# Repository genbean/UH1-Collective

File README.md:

# Heli Collective

A 3D-printed, desk-mounted collective for helicopter flight simulators, modelled on the UH-1 "Huey". It plugs into a PC by USB and shows up as an ordinary game controller, so any sim can use it.

- **The lever** is a 25 mm carbon-fibre tube in a printed base that screws to the desk. It pivots on two ball bearings, a gas strut balances the head's weight, and a knob sets the friction. It travels 32° to a fixed stop. The lever is two-thirds as long as the real one and starts level, so your hand rises about as far as on a real Huey (9.4 in against 9.25 in).
- **The head** is the Huey's collective switch box: GOV RPM, landing light and search light toggles, the SEARCH CONT hat (an 8-way stick), the STOP REL button and the starter trigger. Under it, the twist-grip throttle turns 181° between two hard stops, idle and full open, and stays where you leave it.
- **Sensors:** two AS5600 magnetic angle sensors, one for the lever in the base and one for the throttle in the head. There are no potentiometers to wear out.
- **Electronics:** the HeliSR board, a small PCB that carries a Pro Micro, sits in the head. It reads 16 switch inputs, and the AS5600s over I²C on four sensor ports. Only the USB cable comes out of the base.
- **Software:** the HeliSR firmware and a Windows app, HeliSR Configurator. The app flashes the board, assigns each switch position to a game button and calibrates the axes. Both are based on FreeJoy.

**Interactive exploded views** (point at any part to see what it is): [the base](https://htmlpreview.github.io/?https://github.com/genbean/UH1-Collective/blob/main/Base/renders/rev4_exploded.html), [the base's lever](https://htmlpreview.github.io/?https://github.com/genbean/UH1-Collective/blob/main/Base/renders/rev4_lever_exploded.html), [the head](https://htmlpreview.github.io/?https://github.com/genbean/UH1-Collective/blob/main/Head/renders/HueyHeadR5_Exploded.html), [the head from behind](https://htmlpreview.github.io/?https://github.com/genbean/UH1-Collective/blob/main/Head/renders/HueyHeadR5_Exploded_Rear.html).

More pictures: [from the side](renders/HeliCollective_side.png) and [at the 32° stop](renders/HeliCollective_32deg.png). [`renders/HeliCollective_Assembly.glb`](renders/HeliCollective_Assembly.glb) is the whole collective in 3D; it opens in Windows 3D Viewer or any glTF viewer.

## The parts

Each folder has its own README with the details: how it works, printing, the parts it needs, assembly, and how to rebuild the files.

| Folder | What's in it |
|---|---|
| [`Base/`](Base/README.md) | **MkIII base, Rev 4.** 73 mm (2.87 in) wide, the lever centred on the tube: the pivot on thin-section bearings, the split lever, a shell that encloses it, the gas strut, the brake behind the hub, the stops and the collective's AS5600. Ready-to-print STLs, fit-test coupons, a STEP assembly, renders with every screw labelled, and the scripts that make them. |
| [`Head/`](Head/README.md) | **Huey head, Rev 5.** The switch box in one print, cut to the real UH-1 panels' dimensions, with the throttle grip and its gears, the throttle's AS5600, the starter trigger and the search light hat, and a collision check (`check_r5.py`). STLs and scripts. The BOM lists it. |
| [`PCB/HeliSR/`](PCB/HeliSR/README.md) | **HeliSR Rev 4.0 board.** Sixteen switch inputs, and four I²C ports for the AS5600s, through a PCA9546A switch, in place of the analog inputs. KiCad files, Gerbers, connector pinouts and the assembly order. |
| [`PCB/AS5600/`](PCB/AS5600/README.md) | **AS5600 sensor board Rev 1.0.** The AS5600 on a 23.24 mm square board that fits the base and head, read through a 6 × 2.5 mm diametric magnet, with a JST SH socket on the back that takes a 1:N jumper straight from a HeliSR AX port. Nothing to modify. KiCad files, Gerbers and how to build it. |
| [`PCB/SearchHat/`](PCB/SearchHat/README.md) | **SearchHat Rev 1.0: the SEARCH CONT hat's breakout board.** An ALPS RKJXM1015004 8-direction stick switch on a 22 × 29 mm board that screws to the lower panel's back, with a JST SH socket or wire pads. KiCad files, Gerbers, the pinout and how to build it. |
| [`BOM/`](BOM) | **The bill of materials for the whole collective:** [`Heli_Collective_BOM.xlsx`](BOM/Heli_Collective_BOM.xlsx): every part to buy, with part numbers, where it goes, where to buy it, how many and the price, and a sheet of the printed parts. [`tools/make_bom.py`](tools/make_bom.py) rewrites it (and checks the board's parts against the board file). |
| [`Software/`](Software/README.md) | **HeliSR firmware and HeliSR Configurator**, with their documentation in [`Software/docs/`](Software/docs) and example profiles, including one for this collective. |
| [`renders/`](renders) | Pictures and a 3D model of the complete collective: head Rev 5 on base Rev 4. [`Base/make_renders_r4.py`](Base/make_renders_r4.py) builds them, and base Rev 4's renders, exploded view and screw chart. [`make_diagrams.py`](renders/make_diagrams.py) draws the head's exploded views, screw maps and screw chart from that model. |

## What you need

The full list, with quantities, part numbers, links and prices, is the [BOM spreadsheet](BOM/Heli_Collective_BOM.xlsx). In outline:

**Electronics**
- The HeliSR Rev 4.0 PCB: send [`HeliSR_Rev4.0_Gerbers.zip`](PCB/HeliSR/HeliSR_Rev4.0_Gerbers.zip) to any PCB maker (2 layers, 39.3 × 33.6 mm).
- The SearchHat Rev 1.0 PCB, for the SEARCH CONT hat: send [`SearchHat_Rev1.0_Gerbers.zip`](PCB/SearchHat/SearchHat_Rev1.0_Gerbers.zip) the same way (2 layers, 22 × 29 mm). Its ALPS switch and JST socket are in the BOM.
- The parts that solder onto the HeliSR board, all from Mouser: the BOM lists them with their board positions.
- A **5 V / 16 MHz Pro Micro** (ATmega32U4). This build uses a USB-C clone; the 3.3 V / 8 MHz version isn't supported.
- Two AS5600 sensor boards: send [`AS5600_Rev1.0_Gerbers.zip`](PCB/AS5600/AS5600_Rev1.0_Gerbers.zip) the same way (2 layers, 23.24 mm square). Each takes an AS5600 chip, two 1206 capacitors and a JST SH socket, and goes with a 6 × 2.5 mm diametric magnet; all from Digi-Key.
- JST SR 1.0 mm cables for the board (the sensors' are **1:N** 4-pin jumpers), a 4-core ribbon to lengthen the base sensor's, and a USB-A to USB-C cable. The USB cable runs up through the base and the tube and is spliced inside the head; the BOM's notes explain how.

**Head**
- Four APEM 600H toggle switches, a Same Sky PB4 push button a TE 6 × 6 mm tact switch for the starter trigger, and an ALPS RKJXM1015004 8-way stick switch for the SEARCH CONT hat.
- Four 24 × 2 mm nitrile O-rings, which the throttle grip turns on, a pen spring and four 4 mm board spacers.

**Base**
- Two 6808-2RS thin-section ball bearings (40 × 52 × 7 mm), a 6 in (152 mm), 45 N gas strut with eyelet ends, and a 25 × 23 mm roll-wrapped carbon tube, 500 mm long, used whole.

**Screws, consumables and tools**
- Every screw and nut comes from MonsterBolts in packs of 10, about $23 in all: black-oxide hex socket screws, M2 Phillips flat heads, a stainless M5 hex bolt and plain steel nuts. The BOM and each part's README list them.
- Grease for the bearings and the O-rings, CA glue, hot glue and blue thread-locker; M2, M3, M4 and M5 taps, and 4 mm and 5.2 mm drills for the tube; a soldering iron that can handle 1.0 mm pitch SMD parts.

**Printing and a PC**
- An FDM printer with about 180 mm of build height. The tallest part, the throttle grip, is 173 mm printed upright. The head's panel labels are white, printed in a second filament for the first three layers (an AMS, or a filament change).
- A PC with 64-bit Windows 10 or 11 to set the board up. After that it's a standard USB game controller.
- Python, only if you change the CAD. The STLs are ready to print, and each part's README lists what its scripts need.

## Build order

Each step points to the README that covers it. [`Wiring_Guide.html`](Wiring_Guide.html) has every connector's pins and where each wire goes, with drawings of the three boards and the switches.

1. **Order the parts** from the [BOM](BOM/Heli_Collective_BOM.xlsx), and the PCBs from the Gerbers.
2. **Print the fit-test coupons first**, with the filament and settings you'll use, and try them on your carbon tube, bearings, sensor boards and printed lever dowels: [the base's coupons](Base/README.md#fit-test-coupons) (the 6808 bearing fits, the lever's dowel holes and the tube socket), and the head's O-ring and sensor seat coupons (printed as in [Head, Printing](Head/README.md#printing)). If a fit is off, change its setting in the script and rebuild the STLs.
3. **Build the HeliSR board** ([assembly order](PCB/HeliSR/README.md#assembly-order)) and fit the Pro Micro.
4. **Flash and test it** with HeliSR Configurator: the [quick start](Software/docs/quick-start.md) goes from a bare Pro Micro to a working controller. Check every input now, before it goes into the head. The app picks the HeliSR firmware for you.
5. **Build the two AS5600 sensor boards** ([PCB/AS5600, Assembly](PCB/AS5600/README.md#assembly)), and make the base sensor's lead: a 1:N jumper cut in half with the ribbon spliced between, wire for wire.
6. **Print and assemble the base** ([Base Rev 4, Assembly](Base/README.md#assembly)). The USB cable and the sensor lead go into the lever halves before you close them, the brake strap goes in before the lever, and the tube is drilled, notched and fitted at the end.
7. **Print and assemble the head** ([Head, Assembly](Head/README.md#assembly)): the throttle parts, the starter trigger, the grip on the tube, the head pressed onto the tube, then the board, switches and panels.
8. **Set the two AS5600s' ranges** in HeliSR Configurator's AS5600 helper ([AS5600 guide](Software/docs/as5600.md#setting-the-start-and-stop)): the collective on AX1, the throttle on AX4. The firmware writes each range to its sensor over I²C at every start-up and burns nothing, so it can be set again whenever you like.
9. **Balance and set the friction** ([Base Rev 4, Balance](Base/README.md#balance) and [Brake](Base/README.md#brake)).
10. **Load the UH-1 profile** in HeliSR Configurator, calibrate the axes, and bind the buttons in your sim ([Profiles](Software/docs/profiles.md#uh-1-collective-helisr-head)).

## Status

As of November 2026 the current design is **head Rev 5, base Rev 4 and HeliSR Rev 4.0**.

- **First build:** the first collective was printed and assembled on base Rev 3. What it taught us went into base Rev 4:
  - **Bearings:** the bearing seats fitted perfectly, and the races pressed onto the trunnions a hair too tight.
  - **Strut:** the 45 N strut lifted the lever. Its anchor has since moved, in Rev 4.
  - **Width:** at 130 mm, the base was wider than it needed to be.
- **Base Rev 4:** its first frame, shell and lever were printed and assembled (2026-11-08), and the bearing coupons fitted. Since then it has changed (split lever, brake strap, covers, cable path, lever opening), checked in CAD for collisions and fits through the whole travel and the assembly order; reprint all of it but the strut collar.
- **Head Rev 5:** designed, and checked in CAD for collisions and fits. Earlier head fits were tuned with coupons on an aluminium tube, so check them on the carbon tube.
- **HeliSR Rev 4.0 board:** designed and checked (design rules, and every pad's net against the chips' datasheets), not built yet.
- **Software:** the firmware and HeliSR Configurator in [`Software/`](Software/README.md) support the Rev 4.0 board, with its I²C sensors and their ranges set in the app. They are tested on the PC and a bare Pro Micro only; the Rev 4.0 sensor code against a model of the I²C switch and the AS5600. The software hasn't run on a built board with real switches and sensors.

Expect more changes as the build goes on.

## Credits and licence

- This repository is under the **GNU General Public License v3.0** ([LICENSE](LICENSE)), except where a folder says otherwise.
- **The software in `Software/`** is under the **GNU GPL v3 or later**. It is a modified version of [FreeJoy](https://github.com/FreeJoy-Team/FreeJoy) and [FreeJoyConfiguratorQt](https://github.com/FreeJoy-Team/FreeJoyConfiguratorQt) by the FreeJoy team, ported to the Pro Micro, and isn't made or supported by them. [`Software/NOTICE.md`](Software/NOTICE.md) lists the changes and the third-party components.
- **The original collective: Gazmac52.** This project grew out of [DIY Helicopter Collective Hall Effect](https://www.thingiverse.com/thing:5226353) by **Gazmac52** on Thingiverse, the "MkII" in this project's file names, licensed under [Creative Commons Attribution 4.0](https://creativecommons.org/licenses/by/4.0/). Several components are borrowed from it: the head's throttle grip is built from its grip, modified (`Head/source/MkII-Grip-bore-relieved-25mm.stl`), the HeliSR board reads its switches through 74HC165 shift registers, as Gazmac52's board does, and the head and base are modelled in the MkII's coordinate frames.
- **hotpretzel.** Some components are borrowed from [UH-1 Huey Helicopter Collective](https://www.thingiverse.com/thing:4284120) by **hotpretzel** on Thingiverse, licensed under [Creative Commons Attribution-NonCommercial](https://creativecommons.org/licenses/by-nc/4.0/). The head's faux throttle friction knob is built from hotpretzel's friction knob STL: its wheel profile and flutes were measured off it. So the knob, and the head bodies that carry it (`HueyHeadR4-Body.stl`, `HueyHeadR5-Body.stl` and the scripts' `friction_knob()`), are for **non-commercial use only**, whatever the licence of the folder they're in.
- **Font:** the panels' labels are cut from **Routed Gothic Narrow** by Darren Embry ([webonastick.com/routed-gothic](https://webonastick.com/routed-gothic/)), a digitized Leroy lettering template and the closest free match to the engraved lettering on the real UH-1 panels. It's bundled in [`fonts/routed-gothic/`](fonts/routed-gothic) under the [SIL Open Font License 1.1](fonts/routed-gothic/LICENSE.md), so the panels rebuild on any system.
- **The real UH-1's dimensions:** **Kornskydiver**'s caliper photos of a real UH-1 head (2017) and **dcval**'s scaled drawing of its panels (2025), from the ED Forums thread [Huey Collective Measurements](https://forum.dcs.world/topic/152333-huey-collective-measurements/). Head Rev 5 is built to them. Copies are in [`Head/reference/`](Head/reference/README.md), with credit; they belong to their authors and aren't covered by this repository's licence.

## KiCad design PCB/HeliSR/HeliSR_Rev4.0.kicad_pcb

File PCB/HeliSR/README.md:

# HeliSR Rev 4.0 – Pro Micro + I²C collective board (Huey head)

> **One board built** (see [Checks](#checks-done-on-this-revision)); its I²C lines test clean, but no sensor has
> been read on it yet. Since then the RST button has moved and changed to a PTS810. See [Firmware](#firmware).

A small carrier board for the collective's switch box: a **SparkFun Pro Micro 5V/16 MHz** with **16 switch
inputs** read through two 74HC165 shift registers, and **four I²C ports for AS5600 magnetic angle
sensors**.

The board reads each AS5600's angle digitally over I²C, which doesn't pick up noise on a long cable the way an
analog output does. Every AS5600
has the same I²C address (0x36), so a **PCA9546A I²C switch** on the back of the board gives each port its own
channel, and the firmware talks to one sensor at a time. Each port has its own 2.2 kΩ pull-ups, and all four
ports are built the same, so any port takes a short or a long cable.

| | |
|---|---|
| Board size | 39.3 × 33.64 mm (1.55 × 1.32 in), with four M3 holes. 2 layers, 1.6 mm FR4 |
| Parts | Connectors, the button, the Pro Micro sockets, the shift registers and their parts on the **front**; the I²C switch, its capacitor and all the resistors on the **back**. Every resistor and capacitor is **1206**, for hand soldering |
| Switch inputs | 16, on two 10-pin JST SR/SH 1.0 mm connectors (BM10B-SRSS-TB, SMD) |
| AS5600 ports | 4, each on its own 4-pin JST SR/SH 1.0 mm connector (BM04B-SRSS-G-TB, SMD): **1 SDA, 2 GND, 3 VCC, 4 SCL** |
| I²C switch | PCA9546A (TI PCA9546ADR, SOIC-16 narrow), address 0x70, with its /RESET on a Pro Micro pin |
| Pull-ups | 2.2 kΩ on SDA and SCL of each port (R1–R8); 10 kΩ on the Pro Micro's SDA and SCL (R9, R10) and on /RESET (R11) |
| Button | **RST** (SW1, C&K PTS810 SJM 250 SMTR LFS: 4.2 × 3.2 mm, four pads, all soldered). No PROG buttons: over I²C the firmware sets each sensor's range itself |
| Ground | Both layers poured with ground and stitched together (see [Checks](#checks-done-on-this-revision)) |
| Fab specs | Cheap-fab rules: 0.2 mm clearance, 0.2 mm signal and 0.3 mm VCC/GND tracks, 0.6/0.3 mm vias, holes at least 0.6 mm apart |

Pots and Hall sensors can't go on the AX ports. The Pro Micro still has analog-capable pins free (A2, A3,
4, 6, 8, 9, 10); using one means soldering a wire to the Pro Micro.

## Layout

Viewed from the top, with the USB end on the left:

- **Pro Micro** on two 12-pin sockets, its USB end at the left edge: pins 13–24 (J8) along the top, pins 1–12
  (J7) along the bottom.
- **Under it**: RN1, then C1 | U1 | C3 | U2 | C2, then RN2.
- **Top edge:** J1 (inputs 1-8), AX3 (J13).
- **Bottom edge:** J2 (inputs 9-16), AX1 (J11), then RST (SW1) between AX1 and the bottom-right hole.
- **Far end (right):** AX4 (J14, top), AX2 (J12, bottom).
- **Back:** U3 under the far half of the Pro Micro with C4 beside its VCC pin, R9 and R10 beside its SDA and SCL,
  R11 beside its /RESET; under each port, that port's pair of pull-ups.

Every connector's pins face the board's middle. The JST plugs go in from the top and the cables leave upwards.

Mounting hole centres, in mm from the board's top-left corner (USB end left, J1 up): (3.2, 3.2), (36.1, 3.2),
(3.2, 30.44) and (36.1, 30.44).

## In the Huey head

It fits head Rev 4 and Rev 5 on their spacers and screws. The parts on its front are JST SH height (head Rev 5's
`check_r5.py` takes them as 4.5 mm); the parts on its back (1.75 mm at most) sit in the 4 mm gap the spacers leave
behind the board.

Two things to allow for:
- **AX4 and AX2 are at the far end**: the top of the board in the head, just below the upper
  box's toggles. Their plugs go in from the front, like the others. Leave the wires room to turn there.
- **The throttle's AS5600 needs four wires**, and so does the collective's, which runs up the tube
  from the MkIII base (`Base`). Check the wire channels take four wires.

## Connectors

**J1 (inputs 1-8) and J2 (inputs 9-16)**: 10-pin JST SR/SH 1.0 mm.

| Pin | 1 | 2 | 3 | 4 | 5 | 6 | 7 | 8 | 9 | 10 |
|---|---|---|---|---|---|---|---|---|---|---|
| J1 | GND | IN1 | IN2 | IN3 | IN4 | IN5 | IN6 | IN7 | IN8 | GND |
| J2 | GND | IN9 | IN10 | IN11 | IN12 | IN13 | IN14 | IN15 | IN16 | GND |

Each switch goes between its input pin and GND. The inputs have 10 kΩ pull-ups on the board.

**AX1–AX4 (J11–J14)**: 4-pin JST SR/SH 1.0 mm.

| Pin | 1 | 2 | 3 | 4 |
|---|---|---|---|---|
| AX1–AX4 | SDA | GND | VCC (5 V) | SCL |

The order keeps SDA and SCL apart, with GND beside SDA and VCC beside SCL, which is what you want on a long cable:
twist SDA with GND and SCL with VCC, or use a 4-core cable with those pairs. It is **not** the Qwiic / STEMMA QT
order, on purpose: those boards are 3.3 V and this port is 5 V.

If you make a lead by cutting a pre-made JST SR/SH jumper in half, find which wire is pin 1 with a meter before
soldering the sensor end: the plug is keyed, but the wires may all be one colour.

| Port | Connector | PCA9546A channel | Pull-ups (SDA, SCL) | Suggested use |
|---|---|---|---|---|
| AX1 | J11 | 2 | R1, R2 | Collective (AS5600 in the MkIII base) |
| AX2 | J12 | 1 | R3, R4 | Spare |
| AX3 | J13 | 3 | R5, R6 | Spare |
| AX4 | J14 | 0 | R7, R8 | Throttle (AS5600 in the Huey head) |

The channels follow the board's geometry, not the port numbers: the firmware maps them.

## The I²C circuit

```
Pro Micro "2" SDA ──┬── R9 10k ── VCC                    ┌── R(odd) 2.2k ── VCC
Pro Micro "3" SCL ──┼── R10 10k ── VCC        PCA9546A   ├── port pin 1 SDA ─── AS5600 SDA
Pro Micro "A1" ─────┴── R11 10k ── VCC   ──── SDA/SCL ── SDn/SCn (n = 0..3) ── port pin 4 SCL ─── AS5600 SCL
                                         /RESET, A0-A2 = GND (0x70)           └── R(even) 2.2k ── VCC
```

- **Address:** A0–A2 are tied to GND, so the switch is at **0x70**; the AS5600s are at 0x36 behind it.
- **One channel at a time:** the firmware writes the switch's control register to connect one port, reads that
  sensor, and moves on. Only that port's cable is on the bus, so the long cables don't add up.
- **Pull-ups:** each port has its own 2.2 kΩ pair, on the switch's side of its cable, so each channel is a complete
  I²C bus whether or not the sensor module has pull-ups. With the Pro Micro's 10 kΩ pair in parallel, a low SDA
  sinks 2.3 + 0.5 = 2.8 mA at 5 V, plus whatever the module's own pull-ups add. The weakest part on the bus is the
  PCA9546A, and only while it acknowledges its own writes: TI rates it to sink at least 3 mA at 0.4 V and 6 mA at
  0.6 V (SCPS148I). Every input on the bus reads below 1.5 V (0.3 × 5 V) as low, so anything up to 6 mA works with
  margin. The AS5600 sinks 20 mA at 0.4 V (ams datasheet v1-06), the ATmega32U4 more.
- **/RESET:** R11 holds it high, so the switch works even before the firmware drives A1. Pulling A1 low resets the
  switch (all channels off), which frees a stuck bus. R11 goes to the same 5 V as the chip, as TI's errata ask.
- **Clock speed:** the AS5600 runs up to 1 MHz, but long cables want a slow clock. Plan on **100 kHz**, and less
  (50 or 25 kHz) if a long cable gives errors. Even at 25 kHz, reading all four sensors takes about 10 ms. The clock
  is set in the firmware, not on the board.
- **Cable length:** the limit is the capacitance on each line: 400 pF in the I²C standard (the AS5600 allows
  550 pF). Typical 4-core cable is 50–150 pF per metre, so a metre or more is within it. With 2.2 kΩ and 200 pF
  the rise time is about 0.4 µs, well inside 100 kHz's 1 µs.

## AS5600 sensors

Use the AS5600 sensor board, [`../AS5600`](../AS5600/README.md): an AS5600 wired for 5 V as its datasheet asks,
with no pull-ups of its own, and a 6 × 2.5 mm diametric magnet. It plugs into any AX port with a
**1:N** JST SR jumper (A04SR04SR30K152B); its connector's pins are in the port's order turned end for end to suit
that cable. Nothing on it needs removing, measuring or jumpering.

Nothing is burnt into the chip: the firmware writes each sensor's start and stop angles (ZPOS, MPOS) to its
working registers every time it starts, so the range can be changed as often as you like.

## Pro Micro pins

| Socket pin | Pro Micro pin | Port | Use |
|---|---|---|---|
| 5 | 2 | PD1 | I²C SDA |
| 6 | 3 | PD0 | I²C SCL |
| 15 | 14 | PB3 | Shift register data (U2 QH) |
| 16 | 15 | PB1 | Shift register clock |
| 17 | A0 | PF7 | Shift register load (SH/LD) |
| 18 | A1 | PF6 | PCA9546A /RESET |
| 21, 22, 3/4/23 | VCC, RST, GND | | |

Spare (not connected): TX, RX, 4, 5, 6, 7, 8, 9, 10, 16, A2 and A3. The shift-register pins are the hardware SPI
clock (15) and MISO (14), so a future firmware can read the chain with the SPI unit; pin 16 (MOSI) is then not
free for other use.

## Firmware

The HeliSR firmware in `Software/firmware/HeliSR` is built for this board by `Software/firmware/build.ps1`,
shipped as `firmware\HeliSR_Rev4.0_16MHz.hex`. It:

- reads the shift registers on pins 14 (data), 15 (clock) and A0 (load);
- runs the TWI on pins 2 and 3 at 100 kHz, or 50, 25 or 10 kHz for long cables (set in HeliSR Configurator), connects
  one port's PCA9546A channel at a time and reads its AS5600's ANGLE register (address 0x36), scaled to the analog
  inputs' 0–4092. It also reads STATUS, RAW ANGLE and AGC, for the magnet checks and the Configurator's helper;
- writes each sensor's start and stop to its volatile ZPOS and MPOS at start-up, 1 ms apart, from settings it keeps
  in EEPROM (the Configurator sets them), and CONF as 0 (the chip's factory settings, over anything burnt in); reads
  them back, and writes them again to a sensor that comes back after an error or has lost them. It never burns
  anything;
- maps channels 2, 1, 3, 0 to AX1–AX4 as above. A stuck bus is freed by pulling A1 low (never driving it high), clocking
  out a half-sent byte and sending a STOP; a port that stuck it is left alone for 250 ms;
- treats A2 and A3 as spare analog pins (axis sources 9 and 10), and leaves pin 14 out of the
  spare pins;
- sets the JTD bit in MCUCR at start-up (written twice, as the ATmega32U4 requires). A0 and A1 are also the JTAG
  pins TDI and TDO (PF7, PF6); SparkFun ships the Pro Micro with JTAG off in its fuses (high fuse 0xD8), but a clone
  with JTAG on would otherwise keep both pins from working as plain I/O.

The sensor code is tested on a PC against a model of the PCA9546A and the AS5600 (`Software/firmware/test/host`).
Nothing of this board's firmware has run on the board itself: the shift-register pins, the I²C timing on real
cables, the bus recovery and the sensors' behaviour all wait for one. `Software/PLAN.md` lists what's still to check.

**Only this board.** The firmware is for Rev 4.0 only. Every build carries a tag saying so, INFO reports it, and HeliSR Configurator refuses a `.hex` tagged for another board and asks before flashing an untagged one or a Pro Micro whose firmware reports another board.

## Files

| File | What it is |
|---|---|
| `HeliSR_Rev4.0.kicad_pcb` / `.kicad_pro` | KiCad 9 board |
| `HeliSR_Rev4.0.kicad_dru` | Custom DRC rules for the intentional overlaps (see below) |
| `HeliSR.pretty/`, `fp-lib-table` | Project footprint library: the RST button's footprint (KiCad's `SW_SPST_PTS810`, copied so the board doesn't depend on the KiCad version) |
| `HeliSR_Rev4.0_Gerbers.zip` | Gerbers + drill files |
| `HeliSR_Rev4.0_Top.png`, `HeliSR_Rev4.0_Bottom_mirrored.png` | Board renders |
| `HeliSR_Rev4.0_Input_Map.csv` | Every input → connector pin → chip pin → shift order |
| `tools/` | The scripts that build, route, finish, check and export this board (see Rebuilding) |

## Assembly order

1. **The back first**, while the front is still flat: **U3** (pin 1 dot toward the far end, at the J1 side), then
   **C4** and **R1–R11** (all 1206). R1–R8 are all 2.2 kΩ; R9–R11 10 kΩ.
2. On the front, **U1, U2**, then the 1206 caps **C1, C2, C3**.
3. **RN1, RN2**. The dot (pin 1) goes in the square pad.
4. The JST headers and the RST button: solder all four of its pads.
5. The two Pro Micro sockets last. Use low-profile headers for the sockets and for the Pro Micro's pins (the BOM lists a set): standard ones stand too tall for the USB cable in the head.

## Pro Micro RP2040 compatibility

Every pin the board uses is also there on the **SparkFun Pro Micro RP2040**, whose VCC pin is 3.3 V:
its pins 2 and 3 (GPIO2, GPIO3) can be the RP2040's I2C1 SDA and SCL, and the pull-ups then go to 3.3 V. The AS5600
sensor board is wired for 5 V, so it would need its VDD5V and VDD3V3 joined to run there. There is no RP2040 build of the HeliSR firmware. Not tried.

## DRC rules

`HeliSR_Rev4.0.kicad_dru` covers the intentional overlaps, each rule naming the exact footprint pairs:

- Parts nested under the Pro Micro (resistor networks, shift registers and caps between the sockets).
- The connector rows: the courtyards of J1 and AX3 (J13), and of J2 and AX1 (J11), overlap; the housings don't.
- The M3 holes: their courtyards (6.9 mm across) overlap J1, J2 and the far-end ports AX4 (J14) and AX2 (J12). Every
  pad, track and via is at least 3.5 mm from each hole centre, clear of the M3 nut's corners (3.18 mm) on the front
  and the 6.4 mm spacer on the back.
- Library silkscreen outlines that touch where parts nest.

The rules use `(severity ignore)`, because `kicad-cli` 9.x still reports `(severity exclusion)` rules as errors
(KiCad issue 24264).

## Rebuilding

The board is generated, autorouted and finished by scripts in `tools/`, run with KiCad 9 (its own Python, which has
numpy and PIL) and Freerouting 2.5.0 on a Java 25 runtime. No other Python packages are needed. The board's parts are in
the collective's BOM, [`../../BOM`](../../BOM).

1. `gen_v4.py` places the parts, sets the nets, outline and mounting holes, and exports a DSN. The placement used
   here is `rev40_params.json`.
2. `route_v4.py` runs the generator for a list of placement variants, gives VCC/GND a 0.3 mm class, routes with
   Freerouting, imports the result (`imp_v2.py`) and DRCs it. It routes with the vias 0.7 mm across, so their holes
   end up at least 0.6 mm apart, and imports them at 0.6 mm. This board is the best of the 45 variants in the final sweep
   (U3's position, the pull-ups' offset under the ports, the far-end ports' spacing): complete, 44 router vias.
3. `finish_all_v4.py` widens the router's neck-downs, pours GND on both layers, adds GND stitching vias
   (`stitch_v4.py`), writes the DRC rules and title block (`finish_v4.py`), places the silk labels on both sides
   (`silk_fix_v4.py`), and DRCs the result.
   The board here was routed with the RST button (a TL1015AF) at the far end. `rst_pts810_v4.py` then moved it, once:
   it put a PTS810 between AX1 and the bottom-right hole, where the RST track already ran on the back, cut that track
   there with two vias, removed its run to the far end, moved the RST and J7 labels and refilled the pours.
   `gen_v4.py` now places the PTS810 there itself, so a fresh rebuild doesn't need that step.
   `r11_vias_v4.py` then took the three vias out from under R11 (the AX4_SCL via there is the likely cause of the first
   board's short), added a no-via rule area over R11's courtyard, re-routed what they had joined with Freerouting, and
   added GND stitching vias where pour pieces were cut off. The one AX4_SCL link it left open (R8 to J14 pin 4) was
   joined by one via at 36.26, 13.25, inside J14's outline, clear of every resistor, capacitor and the switch.
   Then the vias were placed again by hand in KiCad (commit "optimizing via placement" and the edits after it): GND
   stitching redone, and the SR_LOAD, IN10, VCC and AX1_SCL vias moved. `via_danger_v4.py` lists every via that
   could pick up solder paste from another net (see Checks).
4. `verify_netlist_v4.py` checks the netlist against the reference board and input map kept in `tools/` for it, and
   against the PCA9546A datasheet's pinout, and writes the input map.
5. `export_v4.py` writes `HeliSR_Rev4.0_Gerbers.zip` and the two renders. `tools/make_bom.py` (at the repo root) then rewrites the
   BOM (it stops if the board's parts and its list disagree).

## Checks done on this revision

- **KiCad 9 DRC:** 0 violations and 0 unconnected items at every severity (with `HeliSR_Rev4.0.kicad_dru`).
- **Netlist:** checked pad by pad by `verify_netlist_v4.py`. J1, J2, U1, U2, RN1, RN2, C1–C3 and SW1 are on the
  same nets as in the reference board, so the inputs and their shift order are unchanged. U3's pins match the
  PCA9546A datasheet (TI SCPS148I): A0 1, A1 2, /RESET 3, SD0–SC1 4–7, GND 8, SD2–SC3 9–12, A2 13, SCL 14, SDA 15,
  VCC 16. Every port, pull-up and Pro Micro pin is as listed above, and every net joins at least two pads.
- **Clearance:** the cheap-fab rules above. All copper is at least 0.5 mm from the edge, and every track and via at
  least 3.7 mm from a hole centre (every pad 4.1 mm). No neck-downs: every signal track is 0.2 mm and every VCC/GND
  track 0.3 mm.
- **Routing:** 992 mm of track, 85 vias: 41 signal (two of them RST's, beside the button) and 44 GND.
- **Vias and solder paste:** no via sits under a resistor, capacitor or the switch between its pads. The vias on
  R5, R6 and R8 sit on those resistors' own pads (same net) and carry them through to the other side.
  `via_danger_v4.py` finds 12 vias closer than 0.5 mm (copper to copper) to another net's SMD pad: IN10 0.20 mm
  from U2.12 (IN11); AX3_SDA 0.25 from U2.1 (SR_LOAD); GND 0.26 from U2.9 (SR_DATA); GND 0.33 from R8's VCC pad;
  AX4_SCL 0.37 from U3.6 (AX2_SDA) and 0.40 from J14.3 (VCC); SR_LOAD 0.38 from U1.9 (SR_CHAIN); GND 0.44 from
  SW1's RST pad; MUX_RST 0.45 from U2.1; GND 0.47 from C2's VCC pad; and IN10 and IN15 at 0.49–0.50 from their J2
  neighbours. Through-hole pads take no paste and aren't counted.
  The I²C lines from U3 to the ports are 6–29 mm long.
- **RST button:** nothing under the PTS810 but its own pads and a GND track; the two RST vias beside it touch its
  outline by 0.1 mm at the RST pads' side. Every via is tented.
- **Decoupling:** C4's VCC pad is 2.65 mm from U3's VCC pin (centre to centre); C1's is 1.8 mm from U1's and C2's
  2.7 mm from U2's.
- **Silkscreen:** every label is 1.0 mm tall with a 0.16 mm stroke, outside every courtyard on its side, and at least
  0.5 mm from the next label. The front names the connectors (J1, J2, AX1–AX4), RST, USB and the front parts; the
  back names U3, C4, R1–R11 and the board.
- **First board (2026-11-14),** built with the earlier layout (a TL1015AF at the far end): the PCA9546A answers and
  reads back every channel setting, IN1–IN16 read open, and AX1–AX3 were clean. AX4's SCL read tied to GND, and still
  did with that switch removed; with J14 and R11 taken off, every pad cleaned and the parts refitted, it cleared, and
  the line test then passed for every port and every pair of ports. That switch's metal frame sat over an AX4_SCL via
  and its frame tabs had no pads, which is why it was replaced anyway. `../../Software/firmware/BoardTest` is the
  sketch that tests the lines.
- **Not checked:** the I²C circuit and the cable lengths are as calculated in the I²C section above, not measured.

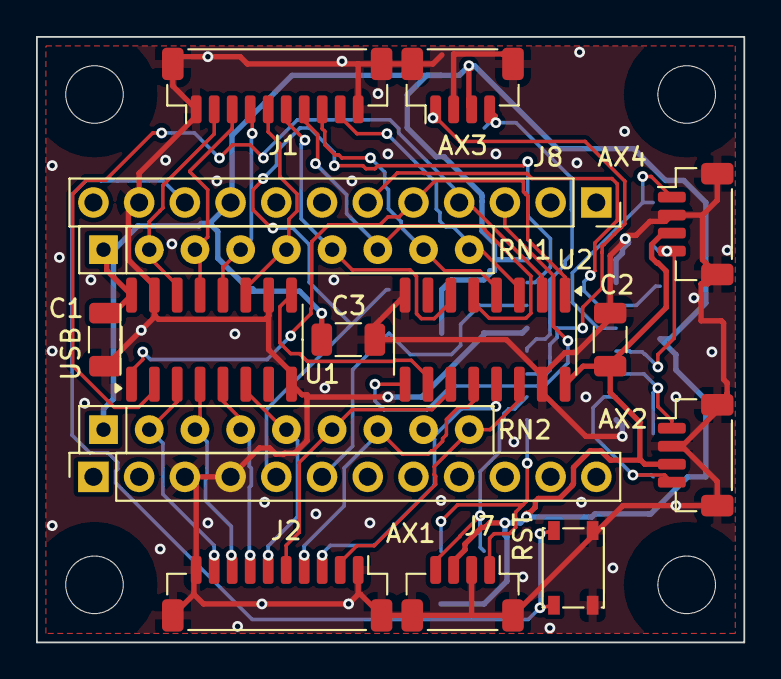
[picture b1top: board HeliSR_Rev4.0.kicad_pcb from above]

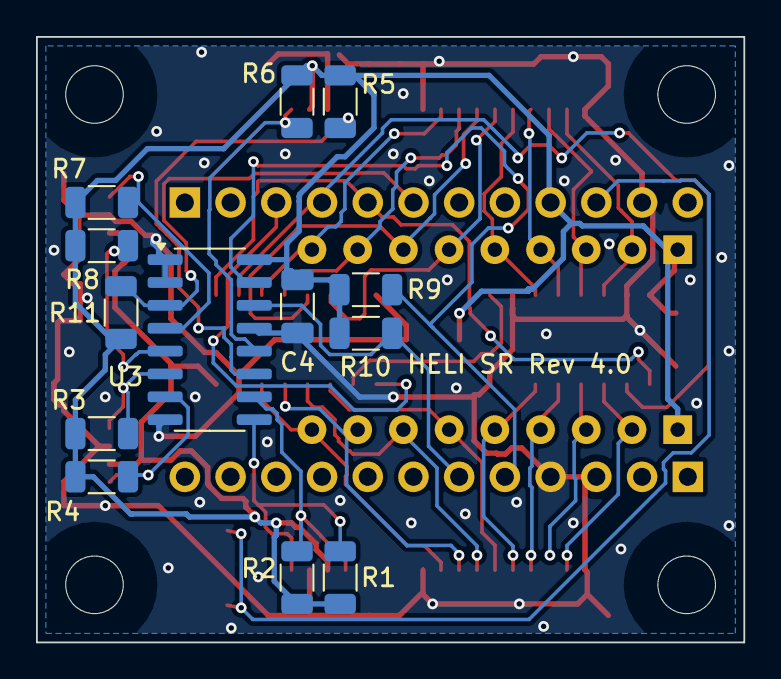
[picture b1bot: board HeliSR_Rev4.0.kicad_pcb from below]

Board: 2 copper layers, 39.3 x 33.6 mm, 33 parts (13 on the bottom side), 34 nets.

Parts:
C1, C2, C4: 100nF; C_1206_3216Metric
C3: 22uF; C_1206_3216Metric
H1, H2, H3, H4: M3; MountingHole_3.2mm_M3
J1: Inputs 1-8; JST_SH_BM10B-SRSS-TB_1x10-1MP_P1.00mm_Vertical
J2: Inputs 9-16; JST_SH_BM10B-SRSS-TB_1x10-1MP_P1.00mm_Vertical
J7: Pro Micro pins 1-12; PinSocket_1x12_P2.54mm_Vertical
J8: Pro Micro pins 13-24; PinSocket_1x12_P2.54mm_Vertical
J11: AX1 (I2C); JST_SH_BM04B-SRSS-TB_1x04-1MP_P1.00mm_Vertical
J12: AX2 (I2C); JST_SH_BM04B-SRSS-TB_1x04-1MP_P1.00mm_Vertical
J13: AX3 (I2C); JST_SH_BM04B-SRSS-TB_1x04-1MP_P1.00mm_Vertical
J14: AX4 (I2C); JST_SH_BM04B-SRSS-TB_1x04-1MP_P1.00mm_Vertical
R1, R2, R3, R4, R5, R6, R7, R8: 2.2k; R_1206_3216Metric
R9, R10, R11: 10k; R_1206_3216Metric
RN1, RN2: 10k x8 bussed; R_Array_SIP9
SW1: PTS810 SJM 250 SMTR LFS; SW_SPST_PTS810
U1, U2: 74HC165; SOIC-16_3.9x9.9mm_P1.27mm
U3: PCA9546A; SOIC-16_3.9x9.9mm_P1.27mm

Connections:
AX1_SCL: J11.4, R2.2, U3.10
AX1_SDA: J11.1, R1.2, U3.9
AX2_SCL: J12.4, R4.2, U3.7
AX2_SDA: J12.1, R3.2, U3.6
AX3_SCL: J13.4, R6.1, U3.12
AX3_SDA: J13.1, R5.1, U3.11
AX4_SCL: J14.4, R8.2, U3.5
AX4_SDA: J14.1, R7.2, U3.4
GND: C1.2, C2.2, C3.2, C4.1, J1.1, J1.10, J1.MP, J2.1, J2.10, J2.MP, J7.3, J7.4, J8.23, J11.2, J11.MP, J12.2, J12.MP, J13.2, J13.MP, J14.2, J14.MP, SW1.2, U1.8, U1.10, U1.15, U2.8, U2.15, U3.1, U3.2, U3.8, U3.13
IN1: J1.2, RN1.2, U1.14
IN2: J1.3, RN1.3, U1.13
IN3: J1.4, RN1.4, U1.12
IN4: J1.5, RN1.5, U1.11
IN5: J1.6, RN1.6, U2.6
IN6: J1.7, RN1.7, U2.5
IN7: J1.8, RN1.8, U2.4
IN8: J1.9, RN1.9, U2.3
IN9: J2.2, RN2.9, U2.14
IN10: J2.3, RN2.8, U2.13
IN11: J2.4, RN2.7, U2.12
IN12: J2.5, RN2.6, U2.11
IN13: J2.6, RN2.5, U1.6
IN14: J2.7, RN2.4, U1.5
IN15: J2.8, RN2.3, U1.4
IN16: J2.9, RN2.2, U1.3
MUX_RST: J8.18, R11.2, U3.3
RST: J8.22, SW1.1
SCL: J7.6, R10.2, U3.14
SDA: J7.5, R9.2, U3.15
SR_CHAIN: U1.9, U2.10
SR_CLK: J8.16, U1.2, U2.2
SR_DATA: J8.15, U2.9
SR_LOAD: J8.17, U1.1, U2.1
VCC: C1.1, C2.1, C3.1, C4.2, J8.21, J11.3, J12.3, J13.3, J14.3, R1.1, R2.1, R3.1, R4.1, R5.2, R6.2, R7.1, R8.1, R9.1, R10.1, R11.1, RN1.1, RN2.1, U1.16, U2.16, U3.16

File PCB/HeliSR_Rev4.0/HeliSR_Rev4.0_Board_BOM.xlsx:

HeliSR Rev 4.0 - board BOM
The parts you solder onto the bare HeliSR Rev 4.0 PCB, checked against the boar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
Boards to build |  | 1 | Edit the yellow cell. Quantities to order and prices follow from it.
# | Reference | Qty per board | Qty to order | Value | Description | Footprint | Manufacturer | Mfr part number | Digi-Key part number | Unit price | Ext. price | Notes
Soldered to the board
1 | U1, U2 | 2 |  | 74HC165 | Shift register, 74HC165, SOIC-16 | SOIC-16_3.9x9.9mm_P1.27mm | Texas Instruments | SN74HC165DR | 296-8250-1-ND | 0.5 |  | Front, under the Pro Micro: fit before the sockets
2 | RN1, RN2 | 2 |  | 10k x8 bussed | Resistor network, 8 x 10 kOhm bussed, SIP-9 | R_Array_SIP9 | Bourns | 4609X-101-103LF | 4609X-101-103LF-ND | 0.39 |  | Pin 1 (dot) is the common pin: it goes in the square pad. Keep upright
3 | C1, C2 | 2 |  | 100nF | Capacitor, 100 nF, 50 V, X7R, 1206 | C_1206_3216Metric | Samsung | CL31B104KBCNNNC | 1276-1017-1-ND | 0.14 |  | Decoupling: C1 beside U1's VCC pin, C2 beside U2's
4 | C3 | 1 |  | 22uF | Capacitor, 22 uF, 10 V, X5R, 1206 | C_1206_3216Metric | Samsung | CL31A226KPHNNNE | 1276-1287-1-ND | 0.47 |  | Bulk supply capacitor, between U1 and U2
5 | U3 | 1 |  | PCA9546A | I2C switch, 4 channels, with reset, SOIC-16 (narrow, D package) | SOIC-16_3.9x9.9mm_P1.27mm | Texas Instruments | PCA9546ADR | 296-21770-1-ND | 1.82 |  | Back. Gives each AS5600 port its own I2C channel (they all answer at 0x36). Not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
6 | C4 | 1 |  | 100nF | Capacitor, 100 nF, 50 V, X7R, 0805 | C_0805_2012Metric | Samsung | CL21B104KBCNNNC | 1276-1003-1-ND | 0.1 |  | Back, beside U3's VCC pin
7 | R1-R8 | 8 |  | 2.2k | Resistor, 2.2 kOhm, 1 %, 1/8 W, 0805 | R_0805_2012Metric | YAGEO | RC0805FR-072K2L | 311-2.20KCRCT-ND | 0.1 |  | Back: the ports' I2C pull-ups, a pair under each port (R1/R2 AX1, R3/R4 AX2, R5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
8 | R9-R11 | 3 |  | 10k | Resistor, 10 kOhm, 1 %, 1/8 W, 0805 | R_0805_2012Metric | YAGEO | RC0805FR-0710KL | 311-10.0KCRCT-ND | 0.1 |  | Back: pull-ups on the Pro Micro's SDA (R9) and SCL (R10), and on U3's /RESET (R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
9 | SW1 | 1 |  | TL1015AF160QG | Tactile switch, SMD, 3.9 x 2.9 mm, gull wing | SW_TL1015AF160QG | E-Switch | TL1015AF160QG | EG4344CT-ND | 0.48 |  | RST, at the far end between AX4 and AX2. The four ground tabs are left unsolder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
10 | J1, J2 | 2 |  | Inputs 1-8, Inputs 9-16 | JST SR/SH header, 10-pin, 1.0 mm, SMD, top entry | JST_SH_BM10B-SRSS-TB_1x10-1MP_P1.00mm_Vertical | JST | BM10B-SRSS-TBT | 455-BM10B-SRSS-TBTCT-ND | 1.19 |  | Switch inputs: J1 IN1-IN8, J2 IN9-IN16. Digi-Key estimates $0.33 tariff each on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
11 | J11-J14 | 4 |  | AX1 (I2C), AX2 (I2C), AX3 (I2C), AX4 (I2C) | JST SR/SH header, 4-pin, 1.0 mm, SMD, top entry | JST_SH_BM04B-SRSS-TB_1x04-1MP_P1.00mm_Vertical | JST | BM04B-SRSS-TBT | 455-BM04B-SRSS-TBTCT-ND | 0.71 |  | AS5600 ports AX1-AX4 (J11-J14): 1 SDA, 2 GND, 3 VCC, 4 SCL. Fit all four, or on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
12 | J7, J8 | 2 |  | Pro Micro pins 1-12, Pro Micro pins 13-24 | Socket header, female, 1x12, 2.54 mm, through hole | PinSocket_1x12_P2.54mm_Vertical | Sullins | PPTC121LFBN-RC | S6100-ND | 0.75 |  | Pro Micro sockets. Fit last
13 | PCB | 1 |  | HeliSR Rev 4.0 | Bare PCB (no parts fitted), 2 layers, 1.6 mm FR4, 39.3 x 33.64 mm |  | OSH Park |  |  | 3.4 |  | Not ordered yet. Priced as Rev 3.0: $10.20 for three bare boards from OSH Park
 |  |  |  |  |  |  |  |  |  | Subtotal
Plugs into the board (the Pro Micro and its headers)
14 | Module | 1 |  |  | Pro Micro 5V/16 MHz, ATmega32U4 |  | SparkFun | 12640 | 1568-12640-ND | 23.99 |  | Runs the HeliSR firmware (Rev 4.0 build). Plugs into J7/J8
15 | Module | 2 |  |  | Pin header, male, 1x12, 2.54 mm |  | Sullins | PRPC012SAAN-RC | 35-PRPC012SAAN-RC-ND | 0.24 |  | Soldered to the Pro Micro
 |  |  |  |  |  |  |  |  |  | Subtotal
 |  |  |  |  |  |  |  |  |  | Total
The bare PCB counts as a third of an OSH Park order of three ($10.20 for Rev 3.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

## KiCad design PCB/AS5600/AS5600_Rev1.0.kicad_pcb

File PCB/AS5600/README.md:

# AS5600 sensor board Rev 1.0

A small board for the AS5600 magnetic angle sensor, 23.24 mm square and 1.6 mm thick, with four M2 holes. It fits the base lever's sensor pocket and the head's sensor pod, and plugs straight into a HeliSR Rev 4.0 AX port with a JST SR jumper: there's nothing to remove, measure or jumper. It goes with a 6 × 2.5 mm diametric magnet (Radial Magnets 9049).

**Why our own board:** the collective first used ready-made AS5600 modules from Amazon. One of them had a short, and every one of the rest had R1–R4 either open or shorted, which didn't match the seller's wiring diagram. This board replaced them.

| Front (chip side, faces the magnet) | Back |
|---|---|
|  |  |

The back render shows J1's pads only: the KiCad install has no 3D model for it.

> **Built.** The board passes KiCad's DRC and the netlist check below, and it is the sensor the collective uses.

## Circuit

The AS5600 runs in 5 V mode, wired as its datasheet asks (ams v1-06, page 3, Pin Description):

| AS5600 pin | Name | Goes to |
|---|---|---|
| 1 | VDD5V | VCC (5 V from the HeliSR), with C1 100 nF to GND |
| 2 | VDD3V3 | C2 1 µF to GND only: in 5 V mode it's the chip's own regulator output |
| 3 | OUT | the OUT test point only |
| 4 | GND | GND |
| 5 | PGO | not connected: the chip's internal pull-up holds it high, so OUT can't burn anything into the chip |
| 6 | SDA | J1 pin 4 |
| 7 | SCL | J1 pin 1 |
| 8 | DIR | GND: the angle rises clockwise, seen from the chip's face |

There are no pull-ups on this board: each HeliSR port has its own 2.2 kΩ pair.

**Test points:** one row under the chip, 2.6 mm apart: plated through-holes (1.5 mm pads, 0.7 mm holes), so a meter or scope probe, or a wire, reaches them from either side. Each is labelled underneath on both sides. Left to right, seen from the front:
- **3V3:** the chip's own regulator output. The board runs on 5 V; this reads about 3.3 V when the chip is powered and working.
- **OUT:** the AS5600's analog output, a voltage that follows the angle, unless something sets it to PWM.
- **GND**, **5V**, **SDA**, **SCL**. Nothing is burnt into the chip; the HeliSR writes the start and stop angles every time it starts.

## Connector and cable

J1, on the back in the middle, is the same JST SH 4-pin header as the HeliSR's AX ports (BM04B-SRSS-TB). Its pins are labelled on the back:

| J1 pin | 1 | 2 | 3 | 4 |
|---|---|---|---|---|
| Signal | SCL | VCC | GND | SDA |

That's the HeliSR port's order (1 SDA, 2 GND, 3 VCC, 4 SCL) turned end for end, to suit the **JST A04SR04SR30K152B** jumper (6 in), which is wired **1:N** (pin 1 to pin 4, 2 to 3, 3 to 2, 4 to 1). With that jumper, each signal lands on its own pin:

| HeliSR AX port | 1 SDA | 2 GND | 3 VCC | 4 SCL |
|---|---|---|---|---|
| through the 1:N jumper to J1 | 4 SDA | 3 GND | 2 VCC | 1 SCL |

**Don't use a 1:1 jumper** (one whose part number ends in **A**): it would put 5 V on the sensor's ground.

- **Throttle (head, AX4):** one whole jumper, sensor to AX4.
- **Collective (base, AX1):** cut a jumper in half and splice the 4-wire ribbon between the halves, each wire to the wire in the same position, so the lead stays 1:N. One plug goes on the sensor, the other on AX1.

## How it fits

- **Front:** U1 sits on the board's centre, over the magnet. The test points are flush with the board; leave them empty (no wires or pins) when it goes in, as the base's cover is close. C1 and C2 sit within 7 mm of the centre, clear of the head's rails (the outer 1.5 mm of two edges) and the base's M2 screw heads (at the corners). The tallest part is the AS5600 itself (1.5 mm); C2 is about 1.15 mm and C1 0.85 mm. The base's cover is 2.0 mm off the board face, and the head's way in is 1.9 mm deep under the board.
- **Back:** only J1 (a 7.9 × 5.3 mm footprint), in the middle.
  - **In the base**, J1 and the plug sit in the 13 mm axial bore behind the pocket, and the lead runs on down the bore. The pocket's four posts and two ledges bear on the board's corners and edges, well away from J1.
  - **In the head**, the board goes in chip down, so J1 faces up into the pod's open top. Plug the jumper in after the board is in its grooves.
- **Holes:** four 2.4 mm holes on a 16.00 mm square, centre to centre, for the base's M2 × 8 screws, so the board goes in any way round. The base's posts are 16.26 mm apart one way; the 2.4 mm holes take the 0.13 mm each side, with 0.07 mm to spare round an M2.

## Parts

Per board, all from Digi-Key.

| Ref | Part | Manufacturer part | Digi-Key | Notes |
|---|---|---|---|---|
| U1 | AS5600, SOIC-8 | ams OSRAM AS5600-ASOM | AS5600-ASOMCT-ND | |
| C1 | 100 nF, 50 V, X7R, 1206 | Samsung CL31B104KBCNNNC | 1276-1017-1-ND | 0.85 mm thick |
| C2 | 1 µF, 16 V, X7R, 1206 | YAGEO CC1206JKX7R7BB105 | 311-1924-1-ND | About 1.15 mm thick. Any 1 µF X7R 1206, 10 V or more, no taller than 1.25 mm will do |
| J1 | JST SH header, 4 pins, 1.0 mm, top entry | JST BM04B-SRSS-TB | 455-BM04B-SRSS-TBCT-ND | The HeliSR's AX port part |
| | Magnet, 6 × 2.5 mm, diametric, N35SH | Radial Magnets 9049 | 469-1075-ND | In the base's sensor cover or the head's magnet shaft |
| | JST SR jumper, 4 positions, 6 in, **1:N** | JST A04SR04SR30K152B | 455-3014-ND | One per sensor |
| | Bare PCB, 2 layers, 1.6 mm, 23.24 mm square | | | Upload `AS5600_Rev1.0_Gerbers.zip` to a board maker (OSH Park makes 3) |

The base's lead also takes a 4-wire ribbon spliced into its jumper (Adafruit 3889, 1 m, Digi-Key 1528-2692-ND).

`AS5600_Rev1.0_BOM.csv` has the same list.

## Assembly

1. **U1** on the front: pin 1 at the triangle on the silkscreen, by C1.
2. **C1** (above U1) and **C2** (left of U1). Neither has a polarity.
3. **J1** on the back, in the middle, its pins toward the labels.
4. **Check with a meter** (unplugged): VCC to GND not shorted (J1 pin 2 to pin 3), and U1's pins 1 and 2 not joined.
5. Fit it: in the base, chip out, screwed down with the four M2 × 8; in the head, chip down into the grooves, a dab of hot glue at the front.

## Direction

DIR is tied to GND, so the angle rises clockwise as seen from the chip's face. The firmware handles either direction:

- **Throttle (head, AX4):** rises from idle to full open, as before.
- **Collective (base, AX1):** the angle falls as the lever lifts. When you set the range, the helper notices this and sets it the other way round; tick **Inverted** on the collective's axis (see `Software/docs/as5600.md`).

## Checks done

- **KiCad DRC:** 0 violations, 0 unconnected (0.2 mm clearance, 0.25 mm signal and 0.4 mm power tracks, 0.6 / 0.3 mm vias).
- **Vias:** seven, only where a net has to change sides (SCL, SDA and VCC to J1) and four to tie the ground pours together. Each is at least 1 mm clear, edge to edge, of every other via, every pad and every part's courtyard on both sides, and none is under a part. `tools/verify_as5600.py` checks this on every build.
- **Netlist:** `tools/verify_as5600.py` checks every pad, the test points included, against tables written out by hand from the AS5600 datasheet and the HeliSR port's pinout through a 1:N cable, not from the generator. It also checks the outline (23.24 mm), the holes, U1 and J1 on the centre, and C1, C2 within 7 mm of it.

## Rebuilding

```bash
.venv/Scripts/python.exe PCB/AS5600/tools/build.py
```

`build.py` runs `gen_as5600.py` (KiCad 9's python) to make `AS5600_Rev1.0.kicad_pcb` with its tracks and ground pours, runs the DRC and `verify_as5600.py`, and writes the Gerbers, the two renders and the BOM. `kicad_run.py` finds KiCad.

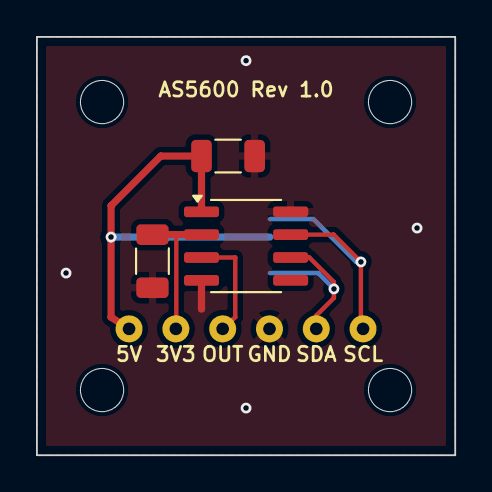
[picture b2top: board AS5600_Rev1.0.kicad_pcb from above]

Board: 2 copper layers, 23.2 x 23.2 mm, 14 parts (1 on the bottom side), 6 nets.

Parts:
C1: 100nF; C_1206_3216Metric
C2: 1uF; C_1206_3216Metric
H1, H2, H3, H4: M2; MountingHole_2.2mm_M2
J1: HeliSR AX port; JST_SH_BM04B-SRSS-TB_1x04-1MP_P1.00mm_Vertical
TP1: 5V; TestPoint_THTPad_D1.5mm_Drill0.7mm
TP2: 3V3; TestPoint_THTPad_D1.5mm_Drill0.7mm
TP3: OUT; TestPoint_THTPad_D1.5mm_Drill0.7mm
TP4: GND; TestPoint_THTPad_D1.5mm_Drill0.7mm
TP5: SDA; TestPoint_THTPad_D1.5mm_Drill0.7mm
TP6: SCL; TestPoint_THTPad_D1.5mm_Drill0.7mm
U1: AS5600; SOIC-8_3.9x4.9mm_P1.27mm

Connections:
GND: C1.2, C2.1, J1.3, J1.MP, TP4.1, U1.4, U1.8
OUT: TP3.1, U1.3
SCL: J1.1, TP6.1, U1.7
SDA: J1.4, TP5.1, U1.6
VCC: C1.1, J1.2, TP1.1, U1.1
VDD3V3: C2.2, TP2.1, U1.2

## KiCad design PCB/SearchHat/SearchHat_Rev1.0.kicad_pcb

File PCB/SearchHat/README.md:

# SearchHat Rev 1.0: breakout board for the SEARCH CONT hat

A small board for hat Rev 4 in the Huey head Rev 5 ([`Head/Hat`](../../Head/Hat/README.md)). It carries an **ALPS RKJXM1015004** 8-direction stick switch with a centre push, and screws to four bosses printed on the back of the lower panel. The switch's body comes through the panel's 13.5 mm hole and the cap goes on its stick.

| Front: faces the panel | Back, mirrored: as you see it from behind |
|---|---|
|  |  |

| | |
|---|---|
| Size | 22 × 29 mm, 2 layers, 1.6 mm FR4, 2 mm corners |
| Holes | Four 2.2 mm holes for M2 × 8 countersunk screws, 8.5 mm from the switch's centre each way (17 mm apart). Every track and both ground pours stop 2.2 mm from each hole's centre, clear of the 3.8 mm screw head |
| Switch | SW1, on the front, centred 11 mm from each long side and 14 mm below the top edge |
| Connector | J1, a 6-pin JST SH 1.0 mm side-entry header (SM06B-SRSS-TB), on the back at the top. The plug goes in from the top edge and the cable leaves upward |
| Wire pads | J2, six 2 mm-pitch plated holes (0.8 mm) along the bottom, to solder wires to instead of J1 |
| Ground | Pours on both sides, joined by eight vias |

## The switch

The RKJXM1015004 has nine pins on two circles (9.9 and 10.7 mm) and a 1.1 mm locating peg. The footprint (`SearchHat.pretty/SW_ALPS_RKJXM1015004`) takes its pin centres from JLCPCB/EasyEDA's footprint for the part (LCSC C97432), which match the ALPS catalog's mounting-hole drawing: 1.0 mm holes for the pins, here with 1.6 mm pads, and a 1.2 mm unplated hole for the peg.

How it's wired inside, from the catalog's circuit diagram:
- **PUSH** (three pins, joined inside) is the common of the four directions. Tilting the stick joins PUSH to A, B, C or D; a diagonal joins two neighbours, so it's an 8-way switch.
- The **centre push** joins COM to PUSH.
- **GND** is the metal frame.

So the board ties PUSH and GND to ground. A–D are the four directions and COM is the centre push. Seen from the front (as you look at the panel), and going by the catalog's lever drawing: **A is up (EXT), C down (RETR), B left (L) and D right (R)**. The silkscreen on the front has an arrow marked EXT pointing up.

## Pinout

| Signal | Switch pin | J1 pin | J2 pad | HeliSR J2 pin | HeliSR input |
|---|---|---|---|---|---|
| R (right) | D | 1 | 1 | 5 | IN12 |
| GND | PUSH ×3, GND | 2 (and the mounting tabs) | 3 | 1 or 10 | |
| RETR (down) | C | 3 | 2 | 3 | IN10 |
| CTR (centre push) | COM | 4 | 5 | 8 | IN15 (game button 17 in the UH-1 profile; leave it off if you don't want a centre button) |
| EXT (up) | A | 5 | 4 | 2 | IN9 |
| L (left) | B | 6 | 6 | 4 | IN11 |

These are the inputs the tact-switch hats used (IN9–IN12 as EXT, RETR, L, R), so the existing profiles work as they are. The centre push is on IN15, game button 17 in the UH-1 profile.

The pin order isn't GND first. On J1 the signals follow the order their switch pins come round the ring, so every track on the back runs without a crossing; on J2 the same goes for the front. The silkscreen names them:
- **J1:** "1" and "6" mark its ends on the back. Up the long edges, "J1: 1R 2GND 3RETR" and "J1: 4CTR 5EXT 6L". Seen from behind, pin 1 is on the right.
- **J2:** each pad's name is under it, on both sides.

**The lead:** cut a 6-pin JST SH jumper (A06SR06SR30K203A) in half, as for the HeliSR's ports. Plug one end into J1 and splice its wires into the HeliSR's J2 loom as in the table. Check pin 1 with a meter: cut jumpers come in both "same side" and "reversed" versions. Or leave J1 off and solder five or six wires to J2.

## Building it

1. **J1 first**, on the back, while the board is flat. Line its pins up on the pads, then tack and solder the two mounting tabs.
2. **SW1** on the front: its peg goes in the 1.2 mm hole, so it only fits one way. Hold it flat against the board and solder its nine pins on the back. It must sit flat: it is what places the stick in the panel's hole.
3. Check with a meter, with nothing pressed: no direction or CTR is joined to GND. Tilt each way and press the middle: each joins its own signal to GND, and each diagonal joins two.

Fitting it to the panel and the cap: [the hat](../../Head/Hat/README.md).

## Checks

- **DRC:** `kicad-cli pcb drc` reports no violations and nothing unconnected. The rules are the HeliSR boards' cheap-fab rules: 0.127 mm minimum track and clearance, with this board's net class at 0.3 mm tracks and 0.2 mm clearance. Two exceptions are written into `SearchHat_Rev1.0.kicad_dru`, each limited to the parts it names:
  - The lower M2 holes' library courtyards overlap J2's by about 0.5 mm. The screw head itself is 0.9 mm from the nearest pad.
  - The left PUSH pin gets one thermal spoke on the back, where R runs past it. A ground track on the back and the front pour join it as well.
- **Fit in the head:** `Head/check_r5.py` places the board, the switch, J1 and a plug with its wires against the body, the toggles and the HeliSR board: all clear. The tightest spot is the end of J1's plug, 2.2 mm below the lower box's top wall. From about 12 mm behind the panel the slot up to the upper box is open, so the wires turn straight back and go up to the HeliSR.

## Not checked

Nothing is ordered or built yet. Still to check on a real part:
- the footprint, against the switch itself: the pin centres come from two sources that agree, but neither is ALPS's own PCB drawing;
- that A is really up, as the catalog's lever drawing reads. If a direction comes out wrong, swap its inputs in the profile, or swap the wires;
- whether a countersunk M2 head sits well on the board's plain 2.2 mm hole. A small washer under each head is fine if it doesn't.

## Files

| File | What it is |
|---|---|
| `SearchHat_Rev1.0.kicad_pcb`, `.kicad_pro`, `.kicad_dru` | The board, its project and its rules (KiCad 9) |
| `SearchHat.pretty/` | The switch's footprint |
| `SearchHat_Rev1.0_Gerbers.zip` | Gerbers with Protel extensions and a job file, plus the PTH and NPTH drill files: send it to any PCB maker |
| `SearchHat_Rev1.0_Top.png`, `_Bottom_mirrored.png` | The pictures above |
| `SearchHat_Rev1.0_mech.json` | The outline, holes and parts' places, measured from the switch's centre. `Head/Hat/hat4_r5.py` reads it, so the panel's bosses always match the board |
| `tools/gen_searchhat.py` | Builds the board from scratch: parts, hand-placed tracks, pours, silkscreen, rules and the JSON |
| `tools/export_searchhat.py` | Writes the Gerbers and the pictures (the HeliSR's export script, sized for this board) |

## Rebuilding

From this folder:

```bash
"$LOCALAPPDATA/Programs/KiCad/9.0/bin/python.exe" tools/gen_searchhat.py .
```

```bash
"$LOCALAPPDATA/Programs/KiCad/9.0/bin/kicad-cli.exe" pcb drc --severity-all --format json -o drc.json SearchHat_Rev1.0.kicad_pcb
```

```bash
python tools/export_searchhat.py SearchHat_Rev1.0.kicad_pcb .
```

Then, in `Head/Hat`, run `python hat4_r5.py ../stl` so the panel's bosses follow any change.

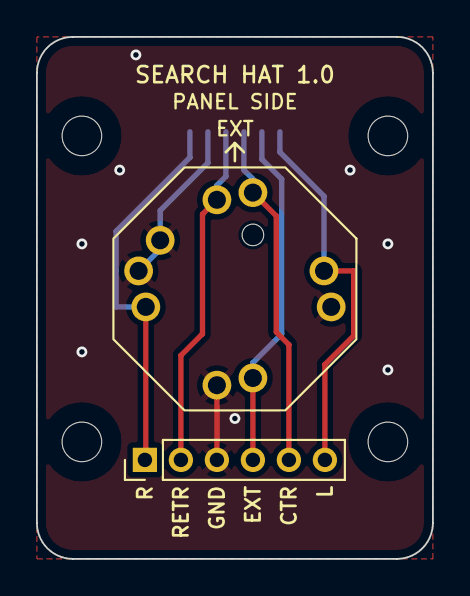
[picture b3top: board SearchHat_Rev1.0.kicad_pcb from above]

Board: 2 copper layers, 22.0 x 29.0 mm, 7 parts (1 on the bottom side), 6 nets.

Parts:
H1, H2, H3, H4: M2; MountingHole_2.2mm_M2
J1: JST SM06B-SRSS-TB; JST_SH_SM06B-SRSS-TB_1x06-1MP_P1.00mm_Horizontal
J2: Wire pads, 2 mm; PinHeader_1x06_P2.00mm_Vertical
SW1: ALPS RKJXM1015004; SW_ALPS_RKJXM1015004

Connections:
CTR: J1.4, J2.5, SW1.1 (COM)
EXT: J1.5, J2.4, SW1.2 (A)
GND: J1.2, J1.MP, J2.3, SW1.6 (PUSH), SW1.7 (GND)
L: J1.6, J2.6, SW1.3 (B)
R: J1.1, J2.1, SW1.5 (D)
RETR: J1.3, J2.2, SW1.4 (C)
